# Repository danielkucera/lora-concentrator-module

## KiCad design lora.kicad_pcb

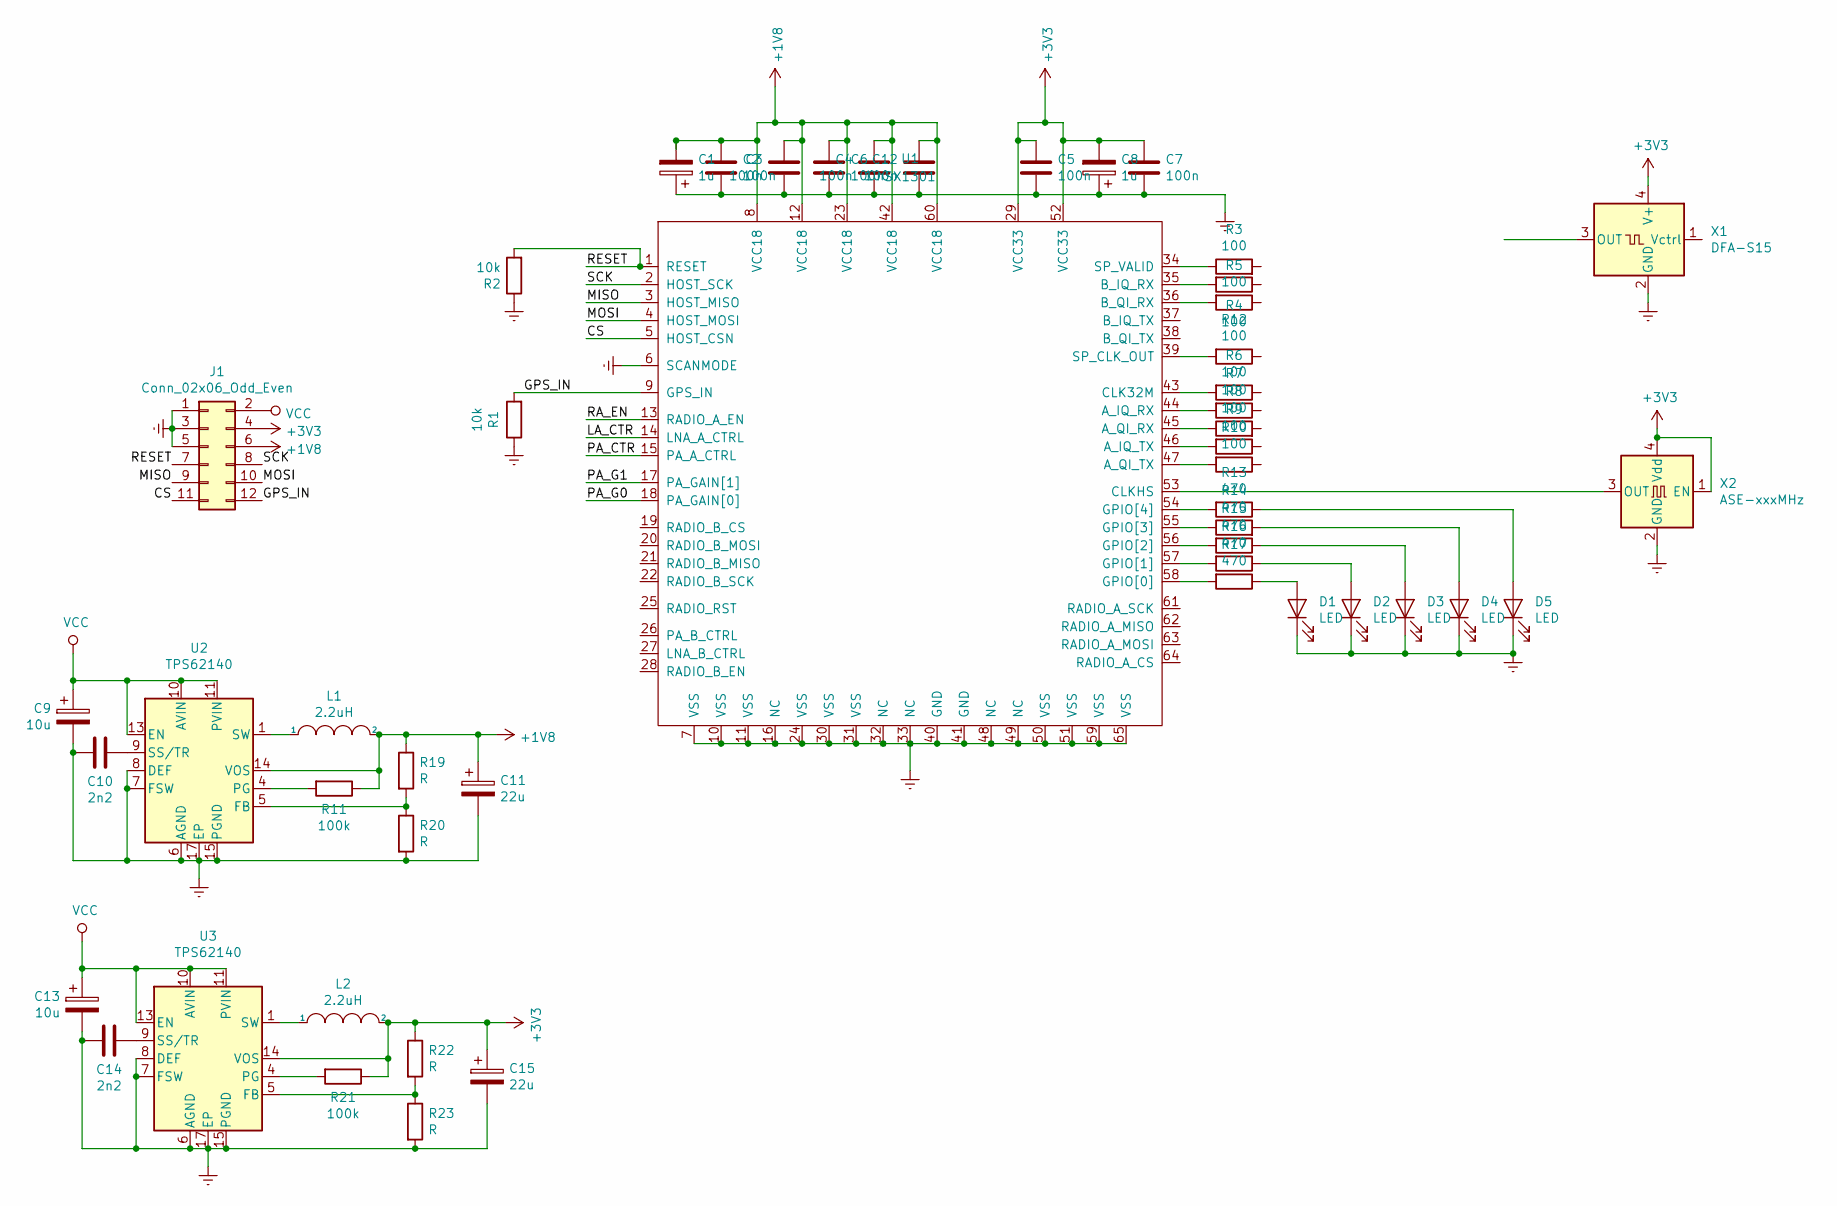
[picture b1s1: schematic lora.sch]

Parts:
C1, C8: 1u; C_0603_1608Metric
C2, C3, C4, C5, C6, C7, C12: 100n; C_0402_1005Metric
C9, C13: 10u; C_0603_1608Metric
C10, C14: 2n2; C_0402_1005Metric
C11, C15: 22u; C_0603_1608Metric
D1, D2, D3, D4, D5: LED; LED_0402_1005Metric
J1: Conn_02x06_Odd_Even; PinHeader_2x06_P2.54mm_Vertical
L1, L2: 2.2uH; L_6.3x6.3_H3
R1, R2: 10k; R_0402_1005Metric
R3, R4, R5, R6, R7, R8, R9, R10, R12: 100; R_0402_1005Metric
R11, R21: 100k; R_0402_1005Metric
R13, R14, R15, R16, R17: 470; R_0402_1005Metric
R19, R20, R22, R23: R; R_0402_1005Metric
U1: SX1301; QFN-64-1EP_9x9mm_P0.5mm_EP7.3x7.3mm_ThermalVias
U2, U3: TPS62140; VQFN-16-1EP_3x3mm_P0.5mm_EP1.68x1.68mm_ThermalVias
X1: DFA-S15; Oscillator_SMD_Fordahl_DFAS15-4Pin_5.0x3.2mm
X2: ASE-xxxMHz; Oscillator_SMD_Abracon_ASE-4Pin_3.2x2.5mm

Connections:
+1V8: C1.2, C2.1, C3.1, C4.1, C6.1, C11.1, C12.1, J1.6, L1.2, R11.1, R19.1, U1.8 (VCC18), U1.12 (VCC18), U1.23 (VCC18), U1.42 (VCC18), U1.60 (VCC18), U2.14 (VOS)
+3V3: C5.1, C7.1, C8.2, C15.1, J1.4, L2.2, R21.1, R22.1, U1.29 (VCC33), U1.52 (VCC33), U3.14 (VOS), X1.4 (V+), X2.1 (EN), X2.4 (Vdd)
/CS: J1.11, U1.5 (HOST_CSN)
/GPS_IN: J1.12, R1.2, U1.9 (GPS_IN)
/LA_CTR: U1.14 (LNA_A_CTRL)
/MISO: J1.9, U1.3 (HOST_MISO)
/MOSI: J1.10, U1.4 (HOST_MOSI)
/PA_CTR: U1.15 (PA_A_CTRL)
/PA_G0: U1.18 (PA_GAIN[0])
/PA_G1: U1.17 (PA_GAIN[1])
/RA_EN: U1.13 (RADIO_A_EN)
/RESET: J1.7, R2.2, U1.1 (RESET)
/SCK: J1.8, U1.2 (HOST_SCK)
Earth: C1.1, C2.2, C3.2, C4.2, C5.2, C6.2, C7.2, C8.1, C9.2, C10.2, C11.2, C12.2, C13.2, C14.2, C15.2, D1.1 (K), D2.1 (K), D3.1 (K), D4.1 (K), D5.1 (K), J1.1, J1.3, J1.5, R1.1, R2.1, R20.2, R23.2, U1.6 (SCANMODE), U1.7 (VSS), U1.10 (VSS), U1.11 (VSS), U1.16 (NC), U1.24 (VSS), U1.30 (VSS), U1.31 (VSS), U1.32 (NC), U1.33 (NC), U1.40 (GND), U1.41 (GND), U1.48 (NC), U1.49 (NC), U1.50 (VSS), U1.51 (VSS), U1.59 (VSS), U1.65 (VSS), U2.6 (AGND), U2.7 (FSW), U2.8 (DEF), U2.15 (PGND), U2.16 (PGND), U2.17 (EP), U3.6 (AGND), U3.7 (FSW), U3.8 (DEF), U3.15 (PGND), U3.16 (PGND), U3.17 (EP), X1.2 (GND), X2.2 (GND)
unnamed: C10.1, U2.9 (SS/TR)
unnamed: C14.1, U3.9 (SS/TR)
unnamed: D1.2 (A), R17.1
unnamed: D2.2 (A), R16.1
unnamed: D3.2 (A), R15.1
unnamed: D4.2 (A), R14.2
unnamed: D5.2 (A), R13.1
unnamed: L1.1, U2.1 (SW), U2.2 (SW), U2.3 (SW)
unnamed: L2.1, U3.1 (SW), U3.2 (SW), U3.3 (SW)
unnamed: R3.1, U1.34 (SP_VALID)
unnamed: R4.2, U1.35 (B_IQ_RX)
unnamed: R5.2, U1.36 (B_QI_RX)
unnamed: R6.2, U1.43 (CLK32M)
unnamed: R7.2, U1.44 (A_IQ_RX)
unnamed: R8.1, U1.45 (A_QI_RX)
unnamed: R9.2, U1.46 (A_IQ_TX)
unnamed: R10.2, U1.47 (A_QI_TX)
unnamed: R11.2, U2.4 (PG)
unnamed: R12.2, U1.39 (SP_CLK_OUT)
unnamed: R13.2, U1.54 (GPIO[4])
unnamed: R14.1, U1.55 (GPIO[3])
unnamed: R15.2, U1.56 (GPIO[2])
unnamed: R16.2, U1.57 (GPIO[1])
unnamed: R17.2, U1.58 (GPIO[0])
unnamed: R19.2, R20.1, U2.5 (FB)
unnamed: R21.2, U3.4 (PG)
unnamed: R22.2, R23.1, U3.5 (FB)
unnamed: U1.53 (CLKHS), X2.3 (OUT)
VCC: C9.1, C13.1, J1.2, U2.10 (AVIN), U2.11 (PVIN), U2.12 (PVIN), U2.13 (EN), U3.10 (AVIN), U3.11 (PVIN), U3.12 (PVIN), U3.13 (EN)

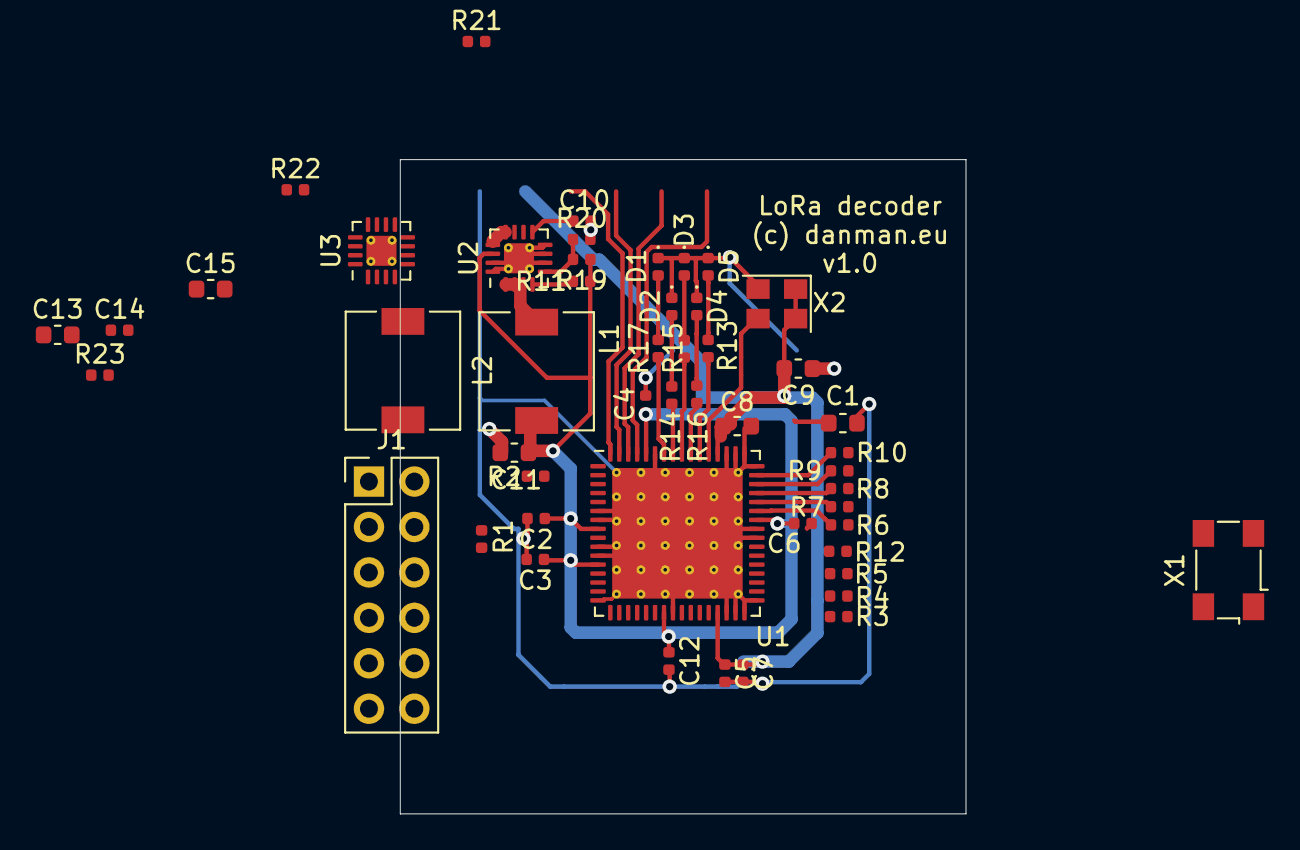
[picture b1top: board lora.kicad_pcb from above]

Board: 2 copper layers, 31.6 x 36.6 mm, 50 parts (0 on the bottom side), 38 nets.

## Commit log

2019-10-11 partialy wired - sequential pins
2019-10-14 v1.0
2019-10-16 added panel PCB
2019-11-11 replaced TPS62141 by TPS62140
2019-11-11 updated pcb TPS, values harmonization
2020-01-17 two regulators, old connectors removed
